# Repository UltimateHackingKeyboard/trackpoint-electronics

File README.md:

Ultimate Hacking Keyboard trackpoint module
===========================================

Contained are the schematics and board layout KiCad files for the [Ultimate Hacking Keyboard](https://ultimatehackingkeyboard.com/) trackpoint module.

Make sure to clone this repo with:

`git clone --recursive git@github.com:UltimateHackingKeyboard/trackpoint-electronics.git`

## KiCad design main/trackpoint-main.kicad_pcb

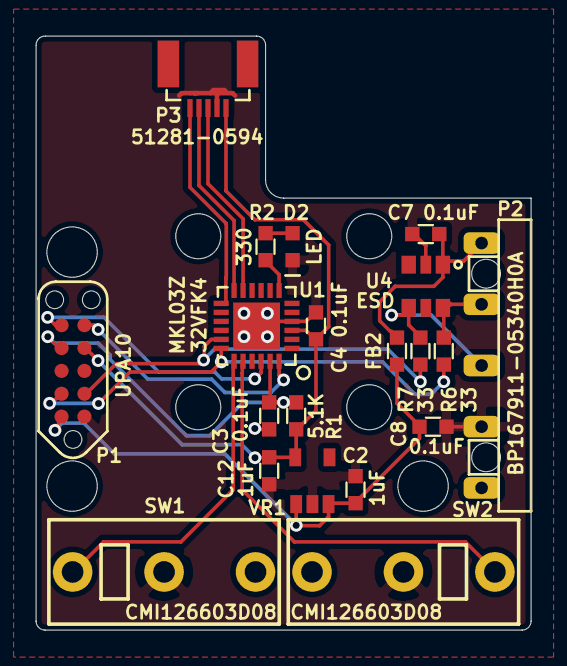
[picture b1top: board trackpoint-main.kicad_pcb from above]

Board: 2 copper layers, 27.5 x 33.0 mm, 20 parts (0 on the bottom side), 18 nets.

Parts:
C2, C12: 1uF; SM0603
C3, C4, C7, C8: 0.1uF; SM0603
D2: LED; SM0603_Diode
FB2: FERRITE_BEAD; SM0603
P1: CONN_10; Tag_Connect_2x5_Header_With_No_Legs_Parallel_Numbering
P2: CONN_5; UHK_Male_Pogo_Pin_v2
P3: CONN_8; FFC_Connector_51281-0594
R1: 5.1K; SM0603
R2: 330; SM0603
R6, R7: 33; SM0603
SW1, SW2: CMI126603D08
U1: MKL03Z32VFK4; QFN-24-1EP_4x4mm_Pitch0.5mm
U4: ESD; SC-74-TVS
VR1: MIC5504-3.3YM5; SOT-23-5

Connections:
+3V3: C4.2, C12.2, P1.7, P3.1, R1.1, U1.3, VR1.5
+5V: C2.2, C8.2, FB2.2, P1.2, VR1.1, VR1.3
/CLK: P3.4, U1.12
/DATA: P3.5, U1.13
/RESET: C3.2, P1.8, R1.2, U1.23
/SCL: P1.3, R7.1, U1.17
/SCL_BOTTOM: P2.3, R7.2, U4.4
/SDA: P1.4, R6.1, U1.18
/SDA_BOTTOM: P2.2, R6.2, U4.5
/SW1: SW1.1, U1.19
/SW2: SW2.1, U1.20
/SWDCLK: P1.10, U1.22
/SWDIO: P1.9, U1.24
/TEST_LED: R2.2, U1.7
/TEST_LED_R: D2.2, R2.1
/TP_RST: P3.3, U1.11
/VCC_BOTTOM: C7.2, FB2.1, P2.1, U4.1
GND: C2.1, C3.1, C4.1, C7.1, C8.1, C12.1, D2.1, P1.1, P2.4, P3.2, SW1.2, SW2.2, U1.4, U1.25, U4.2, VR1.2

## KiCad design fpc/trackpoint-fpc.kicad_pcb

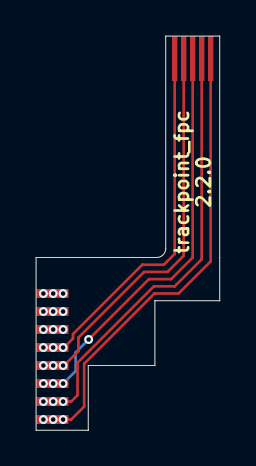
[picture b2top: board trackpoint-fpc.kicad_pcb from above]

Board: 2 copper layers, 10.2 x 21.9 mm, 3 parts (1 on the bottom side), 8 nets.

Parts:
P1, P3: CONN_8; Trackpoint_FPC_8x1_pads
P2: CONN_5; Trackpoint_FPC_5x0.5_pads

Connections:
/CLK: P1.5, P2.2, P3.5
/DATA: P1.4, P2.1, P3.4
/GND: P1.7, P2.4, P3.7
/LBTN: P1.1, P3.1
/MBTN: P1.2, P3.2
/RBTN: P1.3, P3.3
/RESET: P1.6, P2.3, P3.6
/VCC: P1.8, P2.5, P3.8

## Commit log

2019-05-28 Add main and adapter projects.
2019-05-28 Add UGL KiCad lib.
2019-05-28 Add 2 microswitches and a male pogo pin header.
2019-05-28 Finalize the positions of the microswitches.
2019-05-28 Move the pogo pin connector to its final position.
2019-05-28 Add version number and PCB ID text for the main board.
2019-05-28 Add version number and PCB ID for the adapter board.
2019-07-03 Add root project file.
2019-07-03 Remove the adapter board as it's not needed anymore now that the v2 trackpoint module will be used.
2019-07-04 Add fp-lib-table.
2019-07-04 Remove root KiCad project file as this module is only composed of a single board.
2019-07-04 Hoist trackpoint KiCad files to the root directory.
2019-07-04 Rename trackpoint-main.* to trackpoint.*
2019-07-04 Make the ugl module path relative to the project.
2019-07-04 Update board based on new CAD design.
2019-07-06 Add FFC connector.
2019-07-07 Convert circles to holes.
2019-07-07 Improve silk screen.
2019-07-07 Fix hole diameters. Lock FFC connector.
2019-07-07 Update the outline so that the pads of the FFC connector fit.
2019-07-07 Add keepout areas for holes.
2019-07-09 Update keepout areas.
2019-07-11 Update ugl reference.
2019-07-11 Add libraries to project.
2019-07-11 First final version of PCB (schematic added).
2019-07-11 Modified GND plane.
2019-07-13 Add instructions to init submodules.
2019-07-13 Add power symbols.
2019-07-17 Change UPA header pinout.
2019-07-21 Update microswitch footprints.
2019-08-05 Improve silk screen. Rename 5R6 value to 5.6
2019-08-05 Ignore cache, backup and generated files.
2019-08-05 Add netlist.
2019-08-05 Bump version number to 1.0.0
2019-08-07 Add connector part numbers.
2019-08-07 Add UHK logo.
2019-08-09 Adjust silk screen a tiny bit.
2019-08-09 Add UPA14 text.
2019-08-10 Rename UPA14 to UPA10.
2019-08-15 Update hole footprints and apply correct clearances.
2019-08-16 Make logo virtual and make pogo pin connector through-hole.
2019-08-22 Increase the distance between edge and copper to 0.25+ mm.
2019-09-25 Add FPC.
2019-09-25 Add silk screen text.
2019-09-25 Export soldermask layers.
2019-10-27 Update microswitches.
2019-10-27 Update copper pour.
2019-10-27 Update LED footprint.
2020-01-24 Make the test LED and its resistor virtual.
2020-03-05 Add license.
2020-04-05 Disconnect pin 5 of the pogo pin connector.
2020-04-05 Use consistent label font size.
2020-04-12 Update Kailh microswitches.
2020-05-16 Add readme.
2020-05-16 Update ugl-kicad-lib submodule URL.
2020-05-17 Replace resistors from 4.7K to 5.1K and from 47 to 33 ohms.
2020-05-17 Ignore *.sch-bak
2020-05-17 Remove redundant R9, C14, and C15.
2020-05-17 Remove redundant C13.
2020-05-17 Update PCB based on CAD.
2020-05-17 Bump version to 1.1.0
2020-06-08 Use 8 mil tracks and improve component layout.
2020-06-08 Rename microswitch reference designators to SW1 and SW2.
2020-06-08 Slightly improve rooting.
2020-06-08 Bump version to 1.2.0
2020-06-10 Move trackpoint main PCB files to the main directory.
2020-06-10 Rename trackpoint* to trackpoint-main*
2020-06-10 Rename referenced files to trackpoint-main*
2020-06-10 Add toplevel project file.
2020-06-10 Fix schematic library paths.
2020-06-10 Use capitalized library name for the schematic.
2020-06-10 Capitalize UGL library name for the board.
2020-06-11 Tweak plot parameters.
2020-09-18 Tweak plotting options.
2020-09-18 Replace 8 pin, 1 mm pitch connector with 5 pin, 0.5 mm pitch connector.
2020-09-18 Make the CONN_8 silk screen text invisible.
2020-09-18 Connect GND all the way.
2020-09-18 Add new FPC.
2020-09-18 Add pad tracks for the new FPC.
2020-09-19 Add FPC schematic, netlist, and add pad footprints to the board.
2020-09-19 Connect FPC pads.
2020-09-19 Add stiffener to the new FPC.
2020-09-19 Add another 8x0.5 footprint to the other side.
2020-09-19 Update FFC connector part number.
2020-09-19 Update 5x0.5 pads.
2020-09-19 Bump FPC version to 2.0.0
2020-09-19 Change stiffener side.
2020-09-19 Update FFC connector pinout.
2020-09-19 Bump main board version to 2.0.0
2020-10-21 Update FPC based on CAD.
2020-10-21 Bump FPC version to 2.1.0
2020-10-21 Bump PCB version to 2.1.0
2020-12-14 Optimize silk screen for AOI and bump version to 2.1.1
2021-01-02 Remove unneeded edges around pads.
2021-01-02 Reposition silk screen version text.
2021-11-15 Update submodule path.
